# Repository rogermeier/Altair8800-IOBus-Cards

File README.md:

## Sense Switch Input

One of the arguably best features of machines like the Altair 8800, IMSAI 8080, etc., has always been the ability input data and control running programs with the front panel sense switches.

But have you ever wished you had an additional set of switches? 

This card provides exactly that. A set of 8 sense switches at a user-configurable I/O address. Using David Hansel's reference design for his cards, this card also includes a set of jumpers to set the I/O address. By changing the jumpers, multiple of these I/O cards can be installed at the same time and individually addressed.

The header J8 provides a means to input 8 bit data. Note that the inputs use a 3.3V logic level. Driving these inputs will override the switch settings.

To read a value from this card in BASIC, simply execute "PRINT INP(x)", where x is the address of the card.

Schematics and Gerber files for PCB production are in this directory.

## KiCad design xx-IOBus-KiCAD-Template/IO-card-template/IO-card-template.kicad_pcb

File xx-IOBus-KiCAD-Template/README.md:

## IOBus Card Template for KiCAD

KiCAD starter project to design your own IO card compatible with David Hansel's Altair 8800 Simulator IOBus ecosystem (Info: https://github.com/dhansel/Altair8800-IOBus).

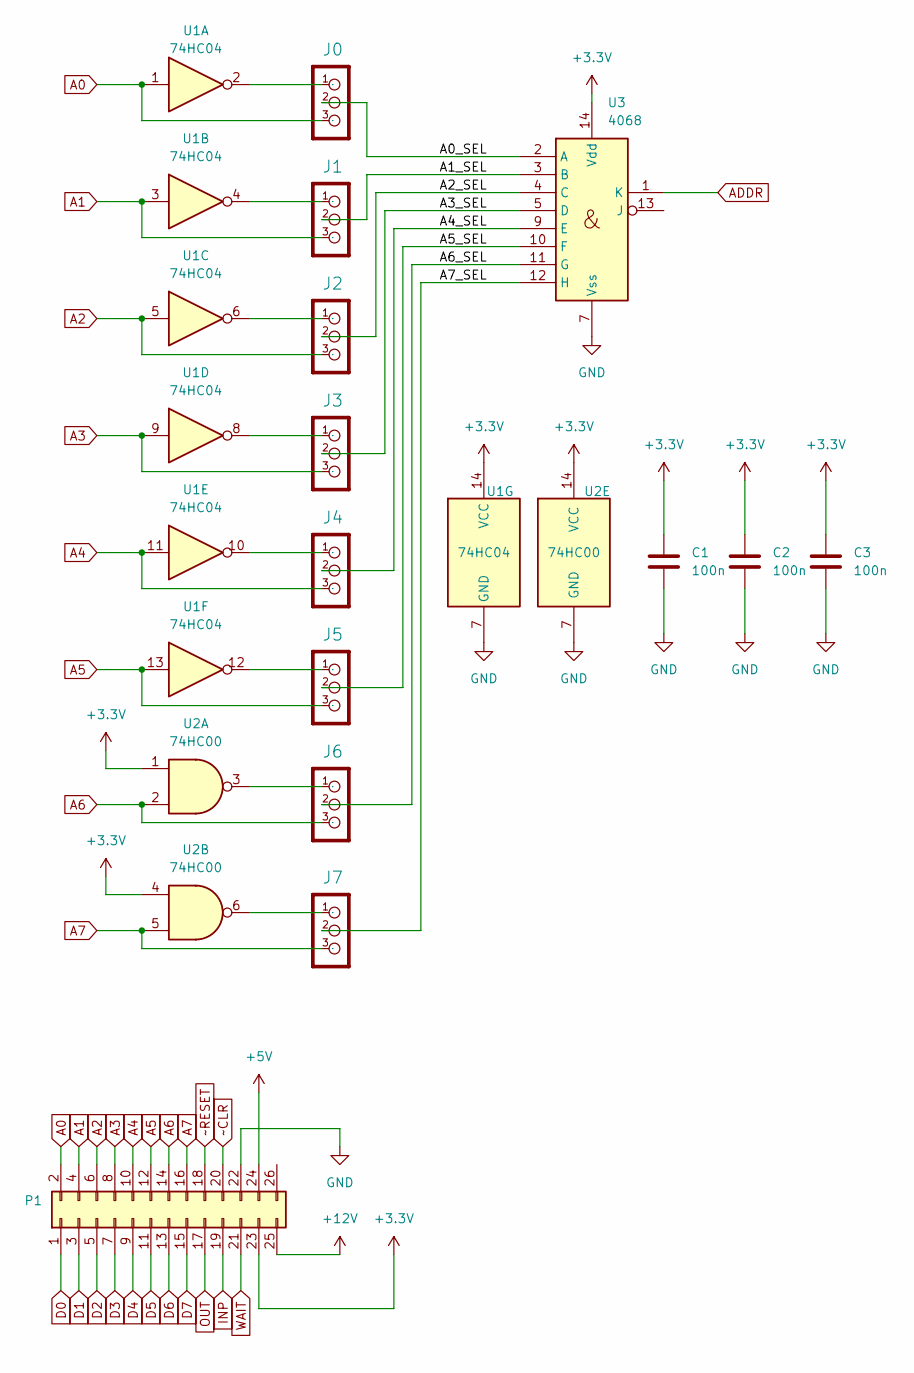
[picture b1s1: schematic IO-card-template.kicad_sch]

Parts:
C1, C2, C3: 100n; C_Disc_D3.0mm_W1.6mm_P2.50mm
J0, J1, J2, J3, J4, J5, J6, J7: CON_HEADER_1X03-PTH; PinHeader_1x03_P2.54mm_Vertical
P1: Conn_02x13_Odd_Even; IDC-Header_2x13_P2.54mm_Horizontal
U1: 74HC04; DIP-14_W7.62mm
U2: 74HC00; DIP-14_W7.62mm
U3: 4068; DIP-14_W7.62mm

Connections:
+3.3V: C1.1, C2.1, C3.1, P1.23, U1.14 (VCC), U2.1, U2.4, U2.14 (VCC), U3.14 (Vdd)
+5V: P1.24
+12V: P1.25
/A0_SEL: J0.2, U3.2 (A)
/A1_SEL: J1.2, U3.3 (B)
/A2_SEL: J2.2, U3.4 (C)
/A3_SEL: J3.2, U3.5 (D)
/A4_SEL: J4.2, U3.9 (E)
/A5_SEL: J5.2, U3.10 (F)
/A6_SEL: J6.2, U3.11 (G)
/A7_SEL: J7.2, U3.12 (H)
A0: J0.3, P1.2, U1.1
A1: J1.3, P1.4, U1.3
A2: J2.3, P1.6, U1.5
A3: J3.3, P1.8, U1.9
A4: J4.3, P1.10, U1.11
A5: J5.3, P1.12, U1.13
A6: J6.3, P1.14, U2.2
A7: J7.3, P1.16, U2.5
ADDR: U3.1 (K)
D0: P1.1
D1: P1.3
D2: P1.5
D3: P1.7
D4: P1.9
D5: P1.11
D6: P1.13
D7: P1.15
GND: C1.2, C2.2, C3.2, P1.22, U1.7 (GND), U2.7 (GND), U3.7 (Vss)
INP: P1.19
unnamed: J0.1, U1.2
unnamed: J1.1, U1.4
unnamed: J2.1, U1.6
unnamed: J3.1, U1.8
unnamed: J4.1, U1.10
unnamed: J5.1, U1.12
unnamed: J6.1, U2.3
unnamed: J7.1, U2.6
OUT: P1.17
WAIT: P1.21
~CLR: P1.20
~RESET: P1.18

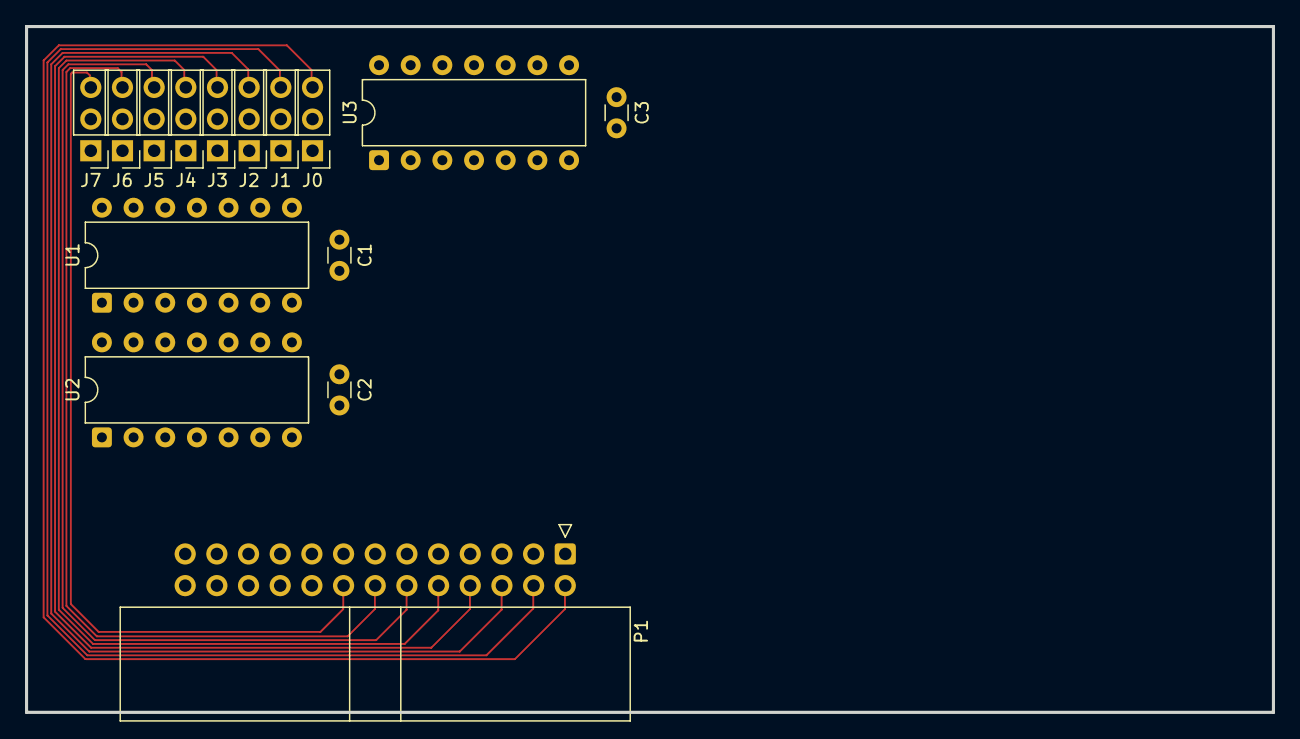
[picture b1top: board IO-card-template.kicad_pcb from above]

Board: 2 copper layers, 100.0 x 55.0 mm, 15 parts (0 on the bottom side), 26 nets.
